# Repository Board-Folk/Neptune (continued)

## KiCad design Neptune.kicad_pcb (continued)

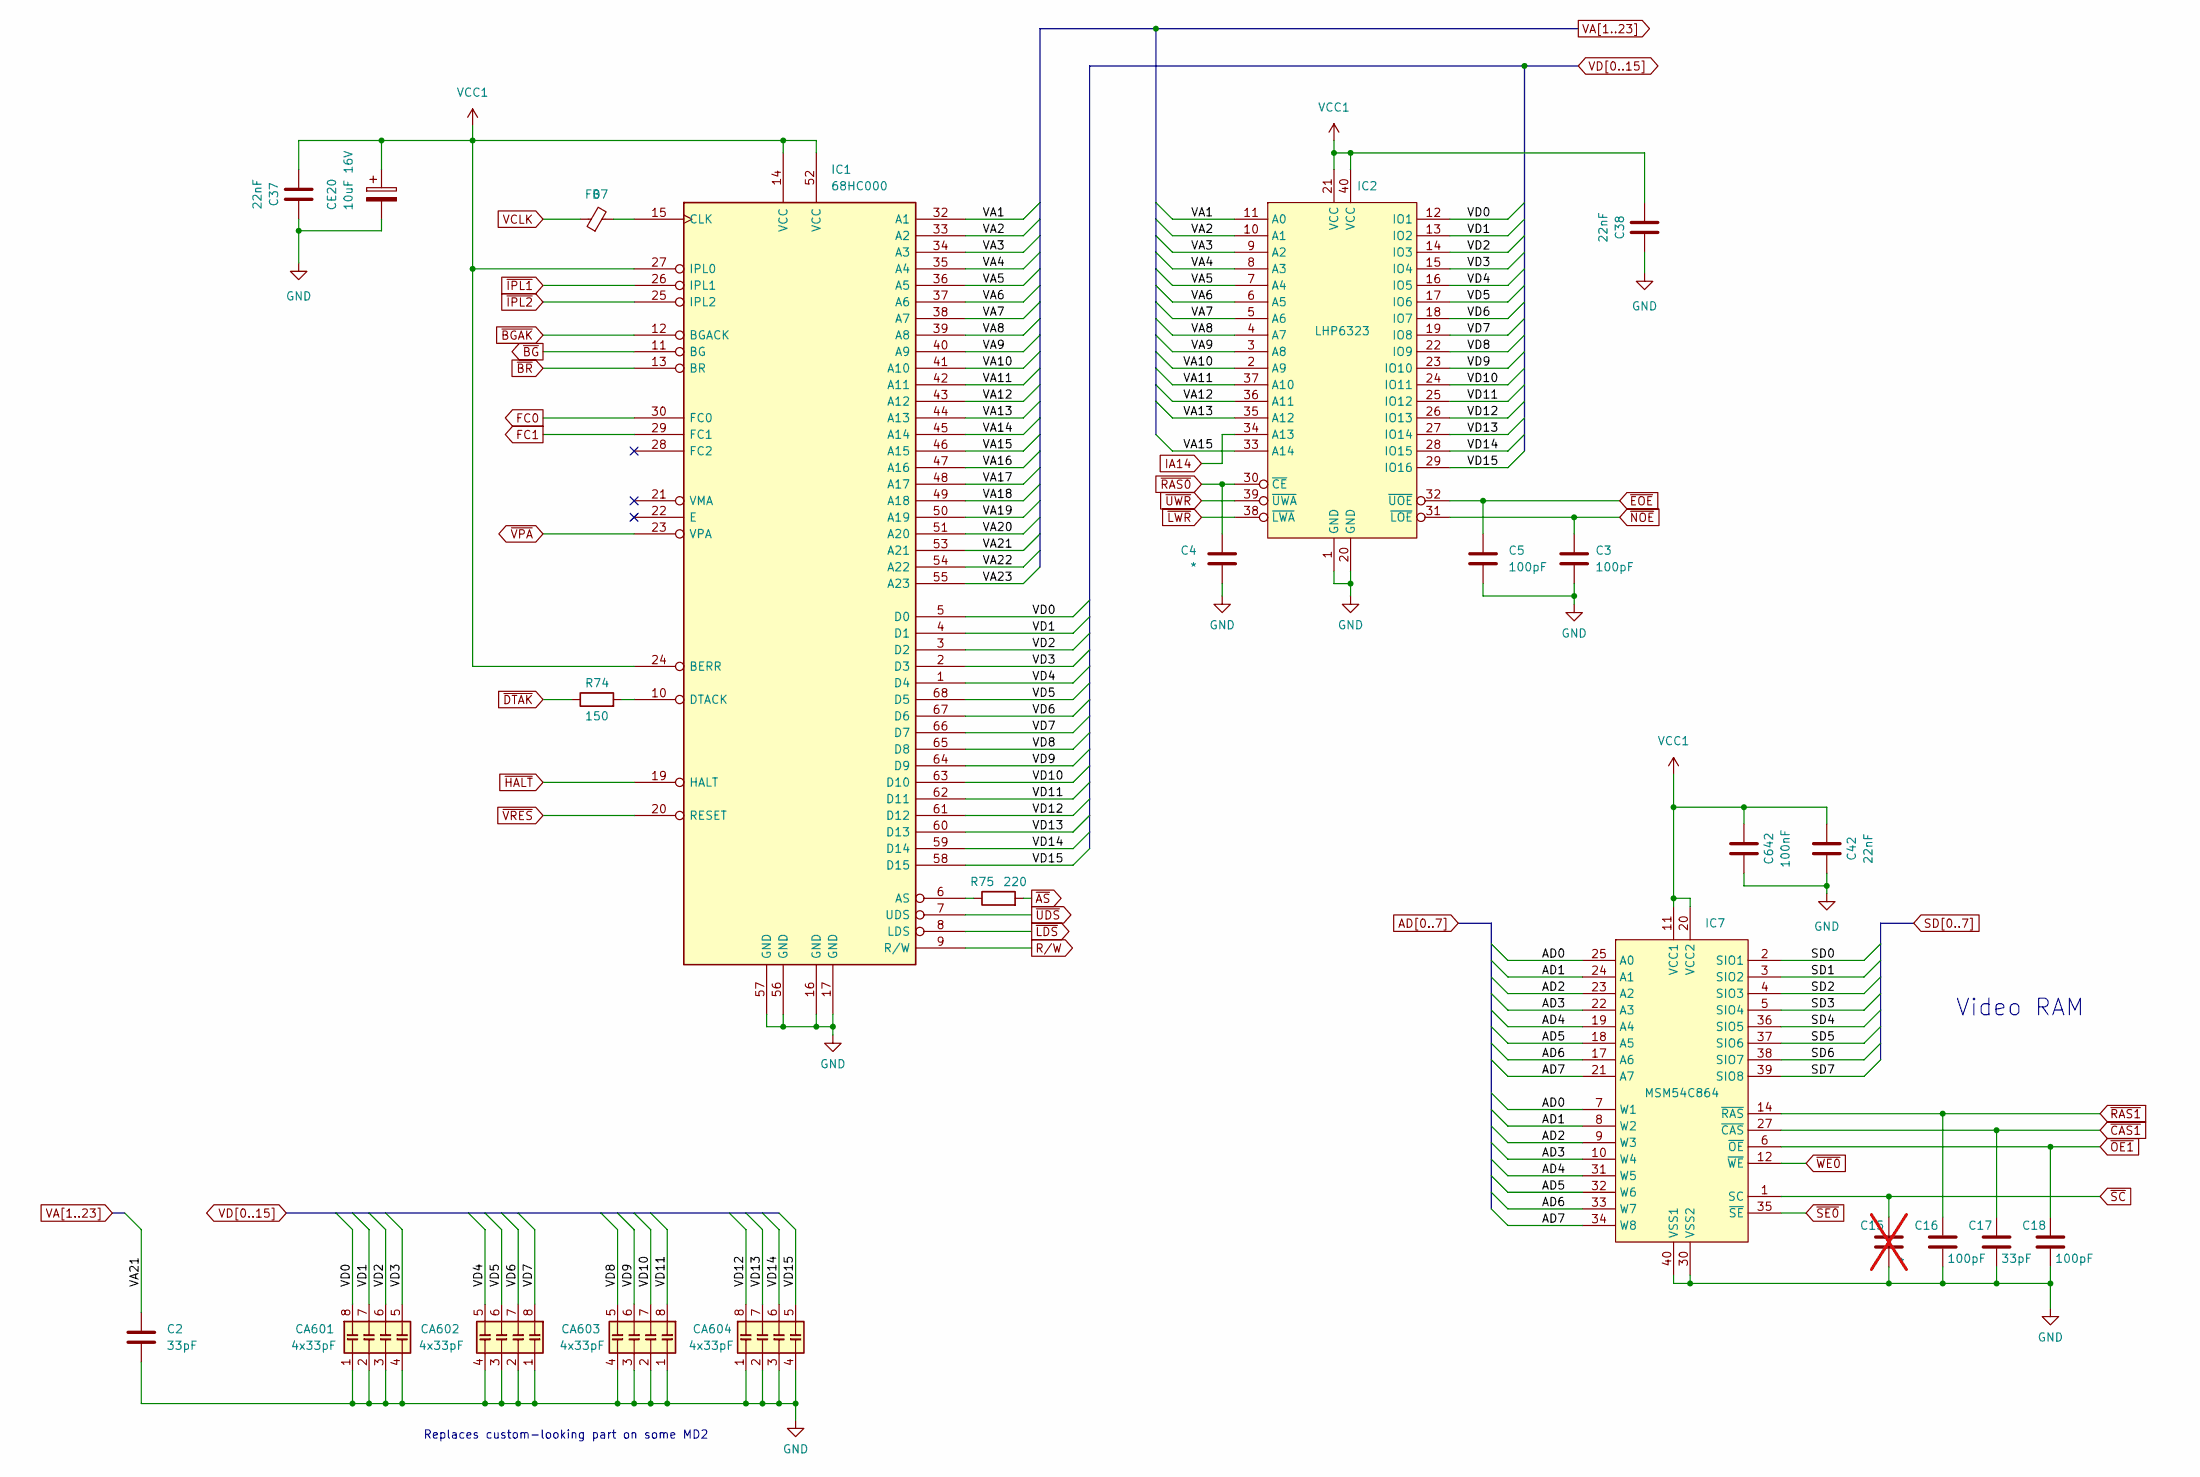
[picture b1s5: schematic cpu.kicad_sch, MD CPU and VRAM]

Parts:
C2, C17: 33pF; C_0805_2012Metric; MPN VJ0805A330FXJPW1BC; LCSC Part # C520060
C3, C5, C16, C18: 100pF; C_0805_2012Metric; MPN VJ0805A101FXJPW1BC; LCSC Part # C1854109
C4: *; C_0805_2012Metric; MPN VJ0805A101FXJPW1BC; LCSC Part # C1854109
C15: *; C_0805_2012Metric; not fitted
C37, C38, C42: 22nF; C_0805_2012Metric; MPN VJ0805Y223JXJPW1BC; LCSC Part # C520037
C642: 100nF; C_0805_2012Metric; MPN VJ0805Y104JXJMT; LCSC Part # C111492
CA601, CA602, CA603, CA604: 4x33pF; R_Array_Convex_4x0603; MPN CA0612KRNPO9BN330; DigiKey 13-CA0612KRNPO9BN330CT-ND
CE20: 10uF 16V; CP_Radial_D5.0mm_P2.50mm
FB7: 0; L_0805_2012Metric; MPN CBG201209U000T; LCSC Part # C91037
IC1: 68HC000; PLCC-68
IC2: LHP6323; SOIC-40
IC7: MSM54C864; SOJ-40
R74: 150; R_0805_2012Metric; MPN CRCW0805150RFKEAHP; LCSC Part # C96210
R75: 220; R_0805_2012Metric; MPN CRCW0805220RFKEAC; DigiKey P220CCT-ND

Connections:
AD0: IC7.7 (W1), IC7.25 (A0); also elsewhere on the board
AD1: IC7.8 (W2), IC7.24 (A1); also elsewhere on the board
AD2: IC7.9 (W3), IC7.23 (A2); also elsewhere on the board
AD3: IC7.10 (W4), IC7.22 (A3); also elsewhere on the board
AD4: IC7.19 (A4), IC7.31 (W5); also elsewhere on the board
AD5: IC7.18 (A5), IC7.32 (W6); also elsewhere on the board
AD6: IC7.17 (A6), IC7.33 (W7); also elsewhere on the board
AD7: IC7.21 (A7), IC7.34 (W8); also elsewhere on the board
AVCC: C37.2, C38.2, C42.2, C642.2, CE20.1, IC1.14 (VCC), IC1.24 (BERR), IC1.27 (IPL0), IC1.52 (VCC), IC2.21 (VCC), IC2.40 (VCC), IC7.11 (VCC1), IC7.20 (VCC2); also elsewhere on the board
FC0: IC1.30 (FC0); also elsewhere on the board
FC1: IC1.29 (FC1); also elsewhere on the board
GND: C2.2, C3.2, C4.2, C5.2, C15.2, C16.2, C17.2, C18.2, C37.1, C38.1, C42.1, C642.1, CA601.1 (R1.1), CA601.2 (R2.1), CA601.3 (R3.1), CA601.4 (R4.1), CA602.1 (R1.1), CA602.2 (R2.1), CA602.3 (R3.1), CA602.4 (R4.1), CA603.1 (R1.1), CA603.2 (R2.1), CA603.3 (R3.1), CA603.4 (R4.1), CA604.1 (R1.1), CA604.2 (R2.1), CA604.3 (R3.1), CA604.4 (R4.1), CE20.2, IC1.16 (GND), IC1.17 (GND), IC1.56 (GND), IC1.57 (GND), IC2.1 (GND), IC2.20 (GND), IC7.30 (VSS2), IC7.40 (VSS1); also elsewhere on the board
IA14: IC2.34 (A13); also elsewhere on the board
unnamed: IC1.6 (AS), R75.1
unnamed: FB7.2, IC1.15 (CLK)
unnamed: IC1.10 (DTACK), R74.2
R/W: IC1.9 (R/W); also elsewhere on the board
SD0: IC7.2 (SIO1); also elsewhere on the board
SD1: IC7.3 (SIO2); also elsewhere on the board
SD2: IC7.4 (SIO3); also elsewhere on the board
SD3: IC7.5 (SIO4); also elsewhere on the board
SD4: IC7.36 (SIO5); also elsewhere on the board
SD5: IC7.37 (SIO6); also elsewhere on the board
SD6: IC7.38 (SIO7); also elsewhere on the board
SD7: IC7.39 (SIO8); also elsewhere on the board
VA1: IC1.32 (A1), IC2.11 (A0); also elsewhere on the board
VA2: IC1.33 (A2), IC2.10 (A1); also elsewhere on the board
VA3: IC1.34 (A3), IC2.9 (A2); also elsewhere on the board
VA4: IC1.35 (A4), IC2.8 (A3); also elsewhere on the board
VA5: IC1.36 (A5), IC2.7 (A4); also elsewhere on the board
VA6: IC1.37 (A6), IC2.6 (A5); also elsewhere on the board
VA7: IC1.38 (A7), IC2.5 (A6); also elsewhere on the board
VA8: IC1.39 (A8), IC2.4 (A7); also elsewhere on the board
VA9: IC1.40 (A9), IC2.3 (A8); also elsewhere on the board
VA10: IC1.41 (A10), IC2.2 (A9); also elsewhere on the board
VA11: IC1.42 (A11), IC2.37 (A10); also elsewhere on the board
VA12: IC1.43 (A12), IC2.36 (A11); also elsewhere on the board
VA13: IC1.44 (A13), IC2.35 (A12); also elsewhere on the board
VA14: IC1.45 (A14); also elsewhere on the board
VA15: IC1.46 (A15), IC2.33 (A14); also elsewhere on the board
VA16: IC1.47 (A16); also elsewhere on the board
VA17: IC1.48 (A17); also elsewhere on the board
VA18: IC1.49 (A18); also elsewhere on the board
VA19: IC1.50 (A19); also elsewhere on the board
VA20: IC1.51 (A20); also elsewhere on the board
VA21: C2.1, IC1.53 (A21); also elsewhere on the board
VA22: IC1.54 (A22); also elsewhere on the board
VA23: IC1.55 (A23); also elsewhere on the board
VCLK: FB7.1; also elsewhere on the board
VD0: CA601.8 (R1.2), IC1.5 (D0), IC2.12 (IO1); also elsewhere on the board
VD1: CA601.7 (R2.2), IC1.4 (D1), IC2.13 (IO2); also elsewhere on the board
VD2: CA601.6 (R3.2), IC1.3 (D2), IC2.14 (IO3); also elsewhere on the board
VD3: CA601.5 (R4.2), IC1.2 (D3), IC2.15 (IO4); also elsewhere on the board
VD4: CA602.5 (R4.2), IC1.1 (D4), IC2.16 (IO5); also elsewhere on the board
VD5: CA602.6 (R3.2), IC1.68 (D5), IC2.17 (IO6); also elsewhere on the board
VD6: CA602.7 (R2.2), IC1.67 (D6), IC2.18 (IO7); also elsewhere on the board
VD7: CA602.8 (R1.2), IC1.66 (D7), IC2.19 (IO8); also elsewhere on the board
VD8: CA603.5 (R4.2), IC1.65 (D8), IC2.22 (IO9); also elsewhere on the board
VD9: CA603.6 (R3.2), IC1.64 (D9), IC2.23 (IO10); also elsewhere on the board
VD10: CA603.7 (R2.2), IC1.63 (D10), IC2.24 (IO11); also elsewhere on the board
VD11: CA603.8 (R1.2), IC1.62 (D11), IC2.25 (IO12); also elsewhere on the board
VD12: CA604.8 (R1.2), IC1.61 (D12), IC2.26 (IO13); also elsewhere on the board
VD13: CA604.7 (R2.2), IC1.60 (D13), IC2.27 (IO14); also elsewhere on the board
VD14: CA604.6 (R3.2), IC1.59 (D14), IC2.28 (IO15); also elsewhere on the board
VD15: CA604.5 (R4.2), IC1.58 (D15), IC2.29 (IO16); also elsewhere on the board
~AS: R75.2; also elsewhere on the board
~BGAK: IC1.12 (BGACK); also elsewhere on the board
~BG: IC1.11 (BG); also elsewhere on the board
~BR: IC1.13 (BR); also elsewhere on the board
~CAS1: C17.1, IC7.27 (~CAS); also elsewhere on the board
~DTAK: R74.1; also elsewhere on the board
~EOE: C5.1, IC2.32 (~UOE); also elsewhere on the board
~HALT: IC1.19 (HALT); also elsewhere on the board
~IPL1: IC1.26 (IPL1); also elsewhere on the board
~IPL2: IC1.25 (IPL2); also elsewhere on the board
~LDS: IC1.8 (LDS); also elsewhere on the board
~LWR: IC2.38 (~LWA); also elsewhere on the board
~NOE: C3.1, IC2.31 (~LOE); also elsewhere on the board
~OE1: C18.1, IC7.6 (~OE); also elsewhere on the board
~RAS0: C4.1, IC2.30 (~CE); also elsewhere on the board
~RAS1: C16.1, IC7.14 (~RAS); also elsewhere on the board
~SC: C15.1, IC7.1 (SC); also elsewhere on the board
~SE0: IC7.35 (~SE); also elsewhere on the board
~UDS: IC1.7 (UDS); also elsewhere on the board
~UWR: IC2.39 (~UWA); also elsewhere on the board
~VPA: IC1.23 (VPA); also elsewhere on the board
~VRES: IC1.20 (RESET); also elsewhere on the board
~WE0: IC7.12 (~WE); also elsewhere on the board

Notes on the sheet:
Replaces custom-looking part on some MD2
Video RAM

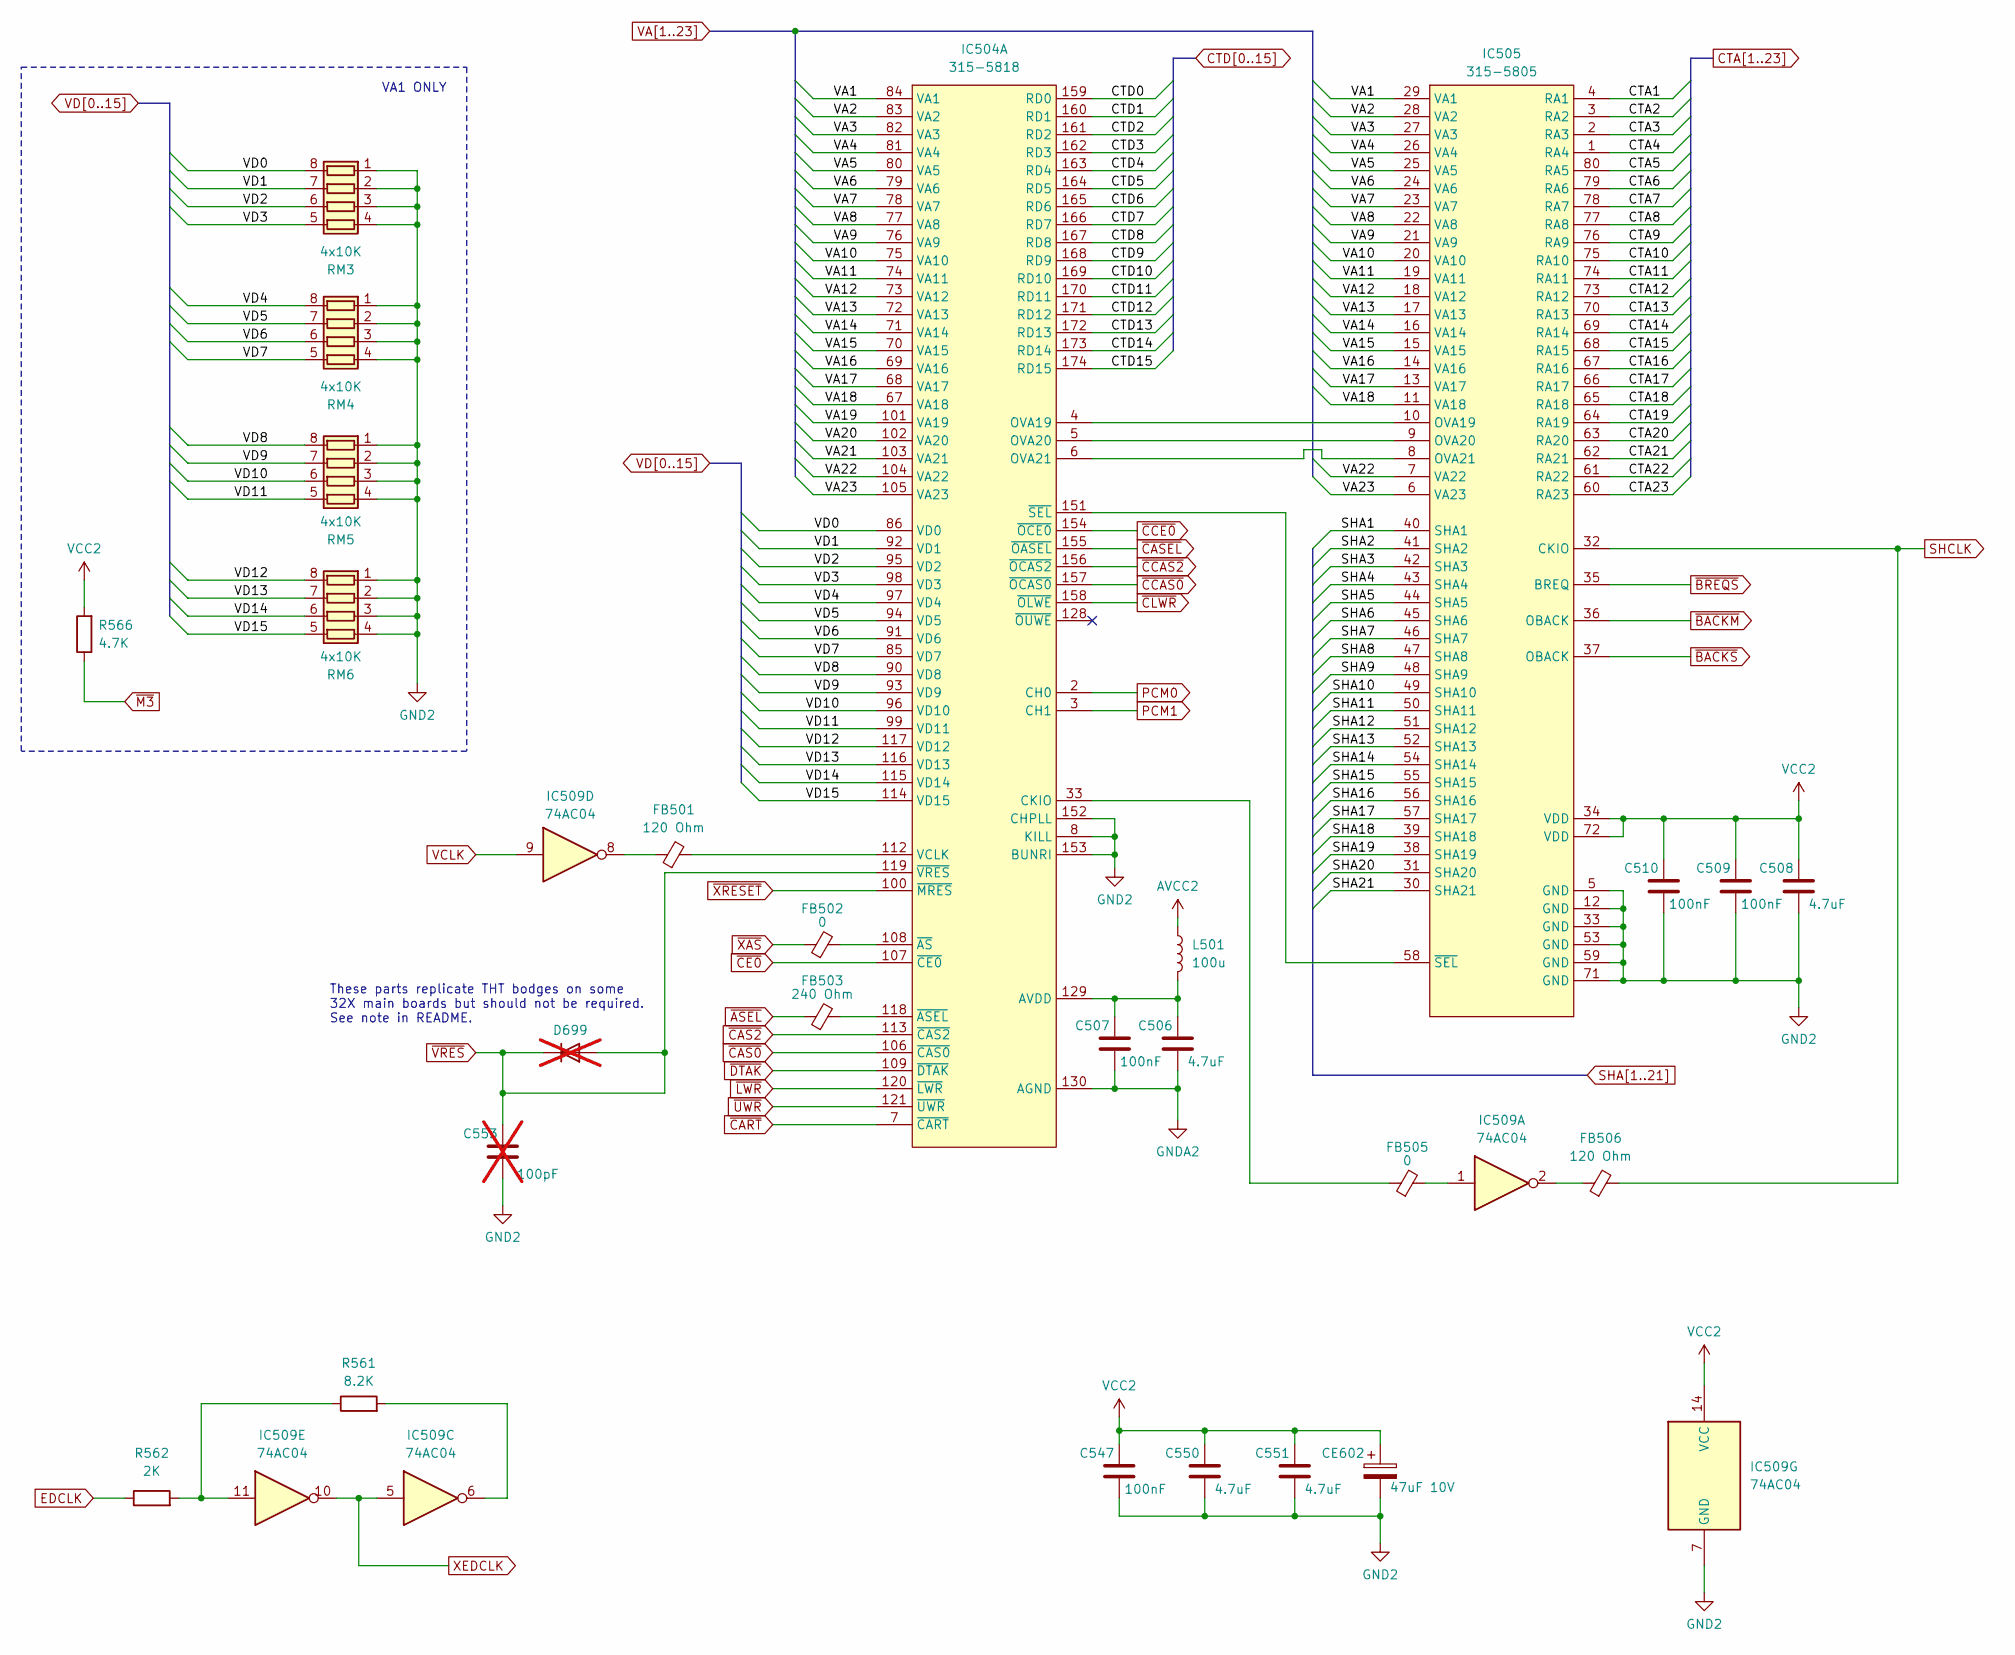
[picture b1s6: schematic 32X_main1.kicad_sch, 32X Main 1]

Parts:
C506, C508, C550, C551: 4.7uF; C_1206_3216Metric; MPN VJ1206V475MXJTW1BC; LCSC Part # C132170
C507, C509, C510, C547: 100nF; C_0805_2012Metric; MPN VJ0805Y104JXJMT; LCSC Part # C111492
C553: 100pF; C_0805_2012Metric; not fitted
CE602: 47uF 10V; CP_Radial_D5.0mm_P2.50mm
D699: D_1206_3216Metric; not fitted
FB501, FB506: 120 Ohm; L_0805_2012Metric; MPN CBG201209U121T; LCSC Part # C41330
FB502, FB505: 0; L_0805_2012Metric; MPN CBG201209U000T; LCSC Part # C91037
FB503: 240 Ohm; L_0805_2012Metric; MPN CBG201209U221T; LCSC Part # C124102
IC504: 315-5818; LQFP-176_24x24mm_P0.5mm
IC505: 315-5805; PQFP-80_14x20mm_P0.8mm
IC509: 74AC04; SO-14_Dual_Purpose_P1.27mm; MPN SN74AC04DR; LCSC Part # C352940
L501: 100u; L_1210_3225Metric_Pad1.42x2.65mm_HandSolder; MPN CMI322513J101KT; LCSC Part # C27775
R561: 8.2K; R_0805_2012Metric; MPN CRCW08058K20FKEA; LCSC Part # C844640
R562: 2K; R_0805_2012Metric; MPN CRCW08052K00JNEA; LCSC Part # C2077049
R566: 4.7K; R_0805_2012Metric; MPN CRCW08054K70JNEAC; LCSC Part # C2077067
RM3, RM4, RM5, RM6: 4x10K; R_Array_Convex_4x0603; MPN YC164-FR-0710KL; LCSC Part # C110924

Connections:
AVCC: C508.1, C509.1, C510.1, C547.1, C550.1, C551.1, CE602.1, IC505.34 (VDD), IC505.72 (VDD), IC509.14 (VCC), L501.1, R566.2; also elsewhere on the board
CTA1: IC505.4 (RA1); also elsewhere on the board
CTA2: IC505.3 (RA2); also elsewhere on the board
CTA3: IC505.2 (RA3); also elsewhere on the board
CTA4: IC505.1 (RA4); also elsewhere on the board
CTA5: IC505.80 (RA5); also elsewhere on the board
CTA6: IC505.79 (RA6); also elsewhere on the board
CTA7: IC505.78 (RA7); also elsewhere on the board
CTA8: IC505.77 (RA8); also elsewhere on the board
CTA9: IC505.76 (RA9); also elsewhere on the board
CTA10: IC505.75 (RA10); also elsewhere on the board
CTA11: IC505.74 (RA11); also elsewhere on the board
CTA12: IC505.73 (RA12); also elsewhere on the board
CTA13: IC505.70 (RA13); also elsewhere on the board
CTA14: IC505.69 (RA14); also elsewhere on the board
CTA15: IC505.68 (RA15); also elsewhere on the board
CTA16: IC505.67 (RA16); also elsewhere on the board
CTA17: IC505.66 (RA17); also elsewhere on the board
CTA18: IC505.65 (RA18); also elsewhere on the board
CTA19: IC505.64 (RA19); also elsewhere on the board
CTA20: IC505.63 (RA20); also elsewhere on the board
CTA21: IC505.62 (RA21); also elsewhere on the board
CTA22: IC505.61 (RA22); also elsewhere on the board
CTA23: IC505.60 (RA23); also elsewhere on the board
CTD0: IC504.159 (RD0); also elsewhere on the board
CTD1: IC504.160 (RD1); also elsewhere on the board
CTD2: IC504.161 (RD2); also elsewhere on the board
CTD3: IC504.162 (RD3); also elsewhere on the board
CTD4: IC504.163 (RD4); also elsewhere on the board
CTD5: IC504.164 (RD5); also elsewhere on the board
CTD6: IC504.165 (RD6); also elsewhere on the board
CTD7: IC504.166 (RD7); also elsewhere on the board
CTD8: IC504.167 (RD8); also elsewhere on the board
CTD9: IC504.168 (RD9); also elsewhere on the board
CTD10: IC504.169 (RD10); also elsewhere on the board
CTD11: IC504.170 (RD11); also elsewhere on the board
CTD12: IC504.171 (RD12); also elsewhere on the board
CTD13: IC504.172 (RD13); also elsewhere on the board
CTD14: IC504.173 (RD14); also elsewhere on the board
CTD15: IC504.174 (RD15); also elsewhere on the board
EDCLK: R562.1; also elsewhere on the board
GND: C506.2, C507.2, C508.2, C509.2, C510.2, C547.2, C550.2, C551.2, C553.2, CE602.2, IC504.8 (KILL), IC504.130 (AGND), IC504.152 (CHPLL), IC504.153 (BUNRI), IC505.5 (GND), IC505.12 (GND), IC505.33 (GND), IC505.53 (GND), IC505.59 (GND), IC505.71 (GND), IC509.7 (GND), RM3.1 (R1.1), RM3.2 (R2.1), RM3.3 (R3.1), RM3.4 (R4.1), RM4.1 (R1.1), RM4.2 (R2.1), RM4.3 (R3.1), RM4.4 (R4.1), RM5.1 (R1.1), RM5.2 (R2.1), RM5.3 (R3.1), RM5.4 (R4.1), RM6.1 (R1.1), RM6.2 (R2.1), RM6.3 (R3.1), RM6.4 (R4.1); also elsewhere on the board
unnamed: FB501.1, IC509.8
unnamed: FB505.2, IC509.1
unnamed: FB506.1, IC509.2
unnamed: C506.1, C507.1, IC504.129 (AVDD), L501.2
unnamed: FB505.1, IC504.33 (CKIO)
unnamed: IC504.4 (OVA19), IC505.10 (OVA19)
unnamed: IC504.5 (OVA20), IC505.9 (OVA20)
unnamed: IC504.6 (OVA21), IC505.8 (OVA21)
unnamed: FB501.2, IC504.112 (VCLK)
unnamed: FB503.2, IC504.118 (~ASEL)
unnamed: FB502.2, IC504.108 (~AS)
unnamed: IC504.151 (~SEL), IC505.58 (~SEL)
unnamed: IC509.6, R561.2
unnamed: IC509.11, R561.1, R562.2
PCM0: IC504.2 (CH0); also elsewhere on the board
PCM1: IC504.3 (CH1); also elsewhere on the board
SHA1: IC505.40 (SHA1); also elsewhere on the board
SHA2: IC505.41 (SHA2); also elsewhere on the board
SHA3: IC505.42 (SHA3); also elsewhere on the board
SHA4: IC505.43 (SHA4); also elsewhere on the board
SHA5: IC505.44 (SHA5); also elsewhere on the board
SHA6: IC505.45 (SHA6); also elsewhere on the board
SHA7: IC505.46 (SHA7); also elsewhere on the board
SHA8: IC505.47 (SHA8); also elsewhere on the board
SHA9: IC505.48 (SHA9); also elsewhere on the board
SHA10: IC505.49 (SHA10); also elsewhere on the board
SHA11: IC505.50 (SHA11); also elsewhere on the board
SHA12: IC505.51 (SHA12); also elsewhere on the board
SHA13: IC505.52 (SHA13); also elsewhere on the board
SHA14: IC505.54 (SHA14); also elsewhere on the board
SHA15: IC505.55 (SHA15); also elsewhere on the board
SHA16: IC505.56 (SHA16); also elsewhere on the board
SHA17: IC505.57 (SHA17); also elsewhere on the board
SHA18: IC505.39 (SHA18); also elsewhere on the board
SHA19: IC505.38 (SHA19); also elsewhere on the board
SHA20: IC505.31 (SHA20); also elsewhere on the board
SHA21: IC505.30 (SHA21); also elsewhere on the board
SHCLK: FB506.2, IC505.32 (CKIO); also elsewhere on the board
VA1: IC504.84 (VA1), IC505.29 (VA1); also elsewhere on the board
VA2: IC504.83 (VA2), IC505.28 (VA2); also elsewhere on the board
VA3: IC504.82 (VA3), IC505.27 (VA3); also elsewhere on the board
VA4: IC504.81 (VA4), IC505.26 (VA4); also elsewhere on the board
VA5: IC504.80 (VA5), IC505.25 (VA5); also elsewhere on the board
VA6: IC504.79 (VA6), IC505.24 (VA6); also elsewhere on the board
VA7: IC504.78 (VA7), IC505.23 (VA7); also elsewhere on the board
VA8: IC504.77 (VA8), IC505.22 (VA8); also elsewhere on the board
VA9: IC504.76 (VA9), IC505.21 (VA9); also elsewhere on the board
VA10: IC504.75 (VA10), IC505.20 (VA10); also elsewhere on the board
VA11: IC504.74 (VA11), IC505.19 (VA11); also elsewhere on the board
VA12: IC504.73 (VA12), IC505.18 (VA12); also elsewhere on the board
VA13: IC504.72 (VA13), IC505.17 (VA13); also elsewhere on the board
VA14: IC504.71 (VA14), IC505.16 (VA14); also elsewhere on the board
VA15: IC504.70 (VA15), IC505.15 (VA15); also elsewhere on the board
VA16: IC504.69 (VA16), IC505.14 (VA16); also elsewhere on the board
VA17: IC504.68 (VA17), IC505.13 (VA17); also elsewhere on the board
VA18: IC504.67 (VA18), IC505.11 (VA18); also elsewhere on the board
VA19: IC504.101 (VA19); also elsewhere on the board
VA20: IC504.102 (VA20); also elsewhere on the board
VA21: IC504.103 (VA21); also elsewhere on the board
VA22: IC504.104 (VA22), IC505.7 (VA22); also elsewhere on the board
VA23: IC504.105 (VA23), IC505.6 (VA23); also elsewhere on the board
VCLK: IC509.9; also elsewhere on the board
VD0: IC504.86 (VD0), RM3.8 (R1.2); also elsewhere on the board
VD1: IC504.92 (VD1), RM3.7 (R2.2); also elsewhere on the board
VD2: IC504.95 (VD2), RM3.6 (R3.2); also elsewhere on the board
VD3: IC504.98 (VD3), RM3.5 (R4.2); also elsewhere on the board
VD4: IC504.97 (VD4), RM4.8 (R1.2); also elsewhere on the board
VD5: IC504.94 (VD5), RM4.7 (R2.2); also elsewhere on the board
VD6: IC504.91 (VD6), RM4.6 (R3.2); also elsewhere on the board
VD7: IC504.85 (VD7), RM4.5 (R4.2); also elsewhere on the board
VD8: IC504.90 (VD8), RM5.8 (R1.2); also elsewhere on the board
VD9: IC504.93 (VD9), RM5.7 (R2.2); also elsewhere on the board
VD10: IC504.96 (VD10), RM5.6 (R3.2); also elsewhere on the board
VD11: IC504.99 (VD11), RM5.5 (R4.2); also elsewhere on the board
VD12: IC504.117 (VD12), RM6.8 (R1.2); also elsewhere on the board
VD13: IC504.116 (VD13), RM6.7 (R2.2); also elsewhere on the board
VD14: IC504.115 (VD14), RM6.6 (R3.2); also elsewhere on the board
VD15: IC504.114 (VD15), RM6.5 (R4.2); also elsewhere on the board
XEDCLK: IC509.5, IC509.10; also elsewhere on the board
~ASEL: FB503.1; also elsewhere on the board
~BACKM: IC505.36 (OBACK); also elsewhere on the board
~BACKS: IC505.37 (OBACK); also elsewhere on the board
~BREQS: IC505.35 (BREQ); also elsewhere on the board
~CART: IC504.7 (~CART); also elsewhere on the board
~CAS0: IC504.106 (~CAS0); also elsewhere on the board
~CAS2: IC504.113 (~CAS2); also elsewhere on the board
~CASEL: IC504.155 (~OASEL); also elsewhere on the board
~CCAS0: IC504.157 (~OCAS0); also elsewhere on the board
~CCAS2: IC504.156 (~OCAS2); also elsewhere on the board
~CCE0: IC504.154 (~OCE0); also elsewhere on the board
~CE0: IC504.107 (~CE0); also elsewhere on the board
~CLWR: IC504.158 (~OLWE); also elsewhere on the board
~DTAK: IC504.109 (~DTAK); also elsewhere on the board
~LWR: IC504.120 (~LWR); also elsewhere on the board
~M3: R566.1; also elsewhere on the board
~UWR: IC504.121 (~UWR); also elsewhere on the board
~VRES: C553.1, D699.1 (K), D699.2 (A), IC504.119 (~VRES); also elsewhere on the board
~XAS: FB502.1; also elsewhere on the board
~XRESET: IC504.100 (~MRES); also elsewhere on the board

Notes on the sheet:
VA1 ONLY
These parts replicate THT bodges on some 32X main boards but should not be required. See note in README.
